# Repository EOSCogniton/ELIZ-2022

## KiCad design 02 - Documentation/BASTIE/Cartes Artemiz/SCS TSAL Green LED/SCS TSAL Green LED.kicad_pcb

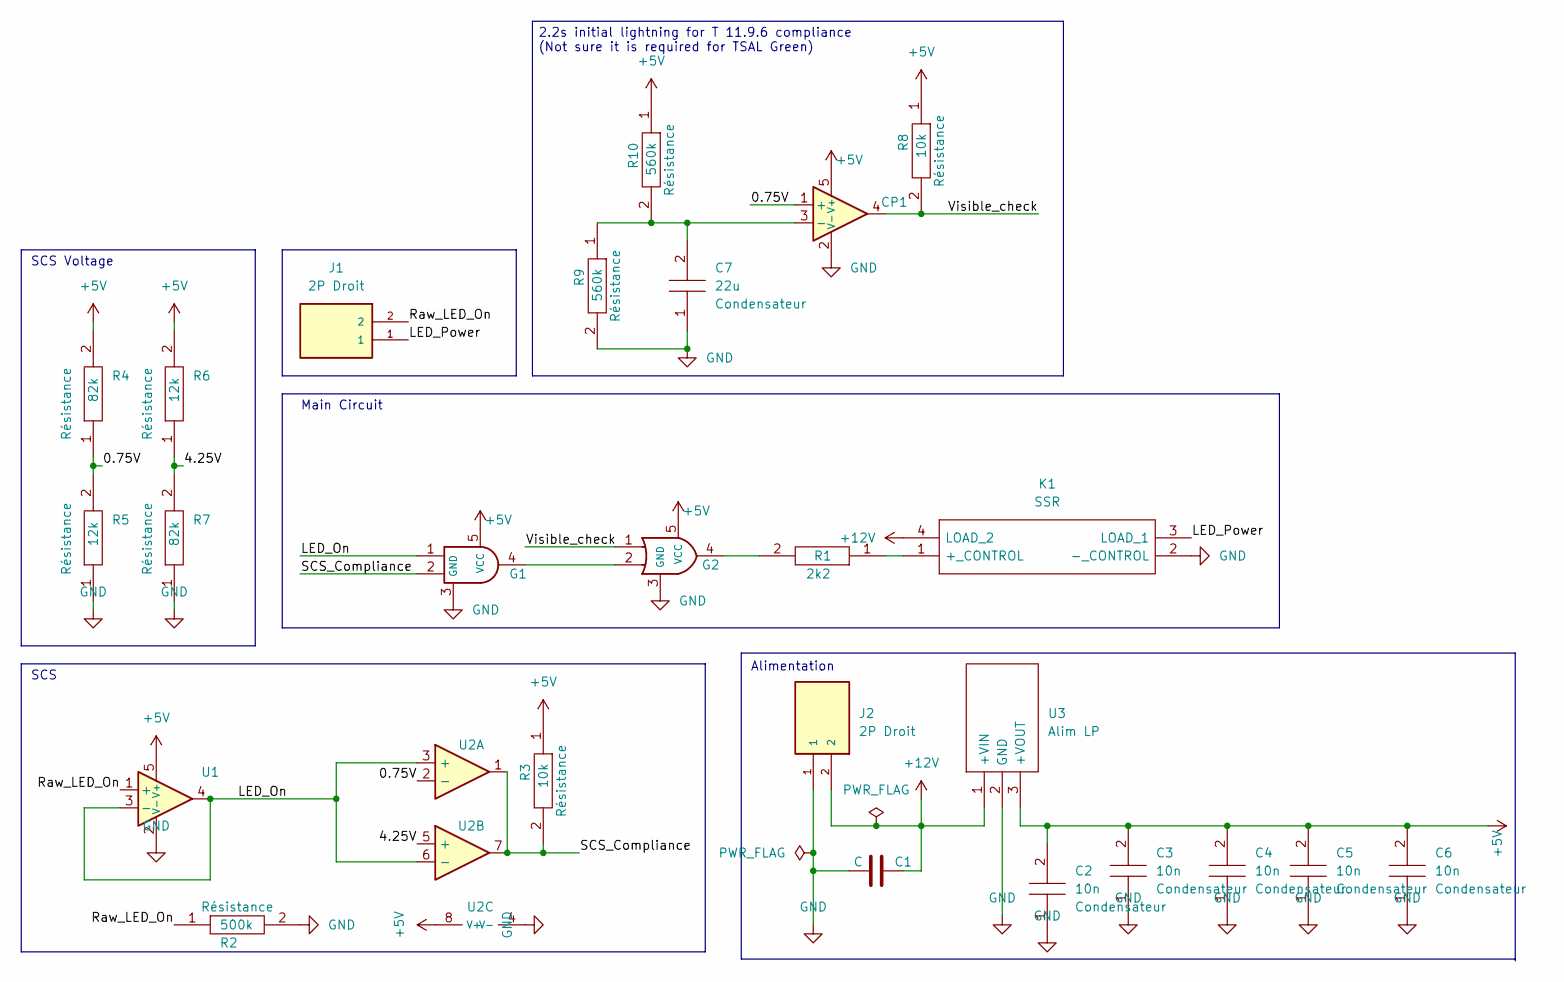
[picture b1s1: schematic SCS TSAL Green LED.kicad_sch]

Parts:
C1: C; CP_Radial_D5.0mm_P2.00mm
C2, C3, C4, C5, C6: 10n; CAPC2012X130N; Manufacturer_Part_Number 0805Y1000104JXT
C7: 22u; CAPC2012X130N; Manufacturer_Part_Number 0805Y1000104JXT
CP1: Comparator; SOT-353_SC-70-5; Manufacturer_Part_Number LMV331M7/NOPB; Mouser Part Number 926-LMV331M7/NOPB
G1: Gate AND SN74AHCT1G08DBVR; SOT95P280X145-5N; Manufacturer_Part_Number SN74AHCT1G08DBVR; Mouser Part Number 595-SN74AHCT1G08DBVR
G2: Gate OR SN74AHCT1G32DBVR; SOT95P280X145-5N; Manufacturer_Part_Number SN74AHCT1G32DBVR; Mouser Part Number 595-SN74AHCT1G32DBVR
J1, J2: 2P Droit 2-11-2022; MOLEX_22-11-2022; PARTREV BD8
K1: SSR CPC1394GR; CPC1394GR; Manufacturer_Part_Number CPC1394GR; Mouser Part Number 849-CPC1394GR
R1: 2k2; RESC3216X70N; Manufacturer_Part_Number RK73H2BLTDD2152F; Mouser Part Number N/A
R2: 500k; RESC3216X70N; Manufacturer_Part_Number RK73H2BLTDD2152F; Mouser Part Number N/A
R3, R8: 10k; RESC3216X70N; Manufacturer_Part_Number RK73H2BLTDD2152F; Mouser Part Number N/A
R4, R7: 82k; RESC3216X70N; Manufacturer_Part_Number RK73H2BLTDD2152F; Mouser Part Number N/A
R5, R6: 12k; RESC3216X70N; Manufacturer_Part_Number RK73H2BLTDD2152F; Mouser Part Number N/A
R9, R10: 560k; RESC3216X70N; Manufacturer_Part_Number RK73H2BLTDD2152F; Mouser Part Number N/A
U1: ${SIM.PARAMS}; SOT-353_SC-70-5_Handsoldering; Manufacturer_Part_Number TLV9061QDCKRQ1; Mouser Part Number 595-TLV9061QDCKRQ1
U2: Opamp_Dual; TSSOP-8_4.4x3mm_P0.65mm; Manufacturer_Part_Number LMV393IPWR; Mouser Part Number 595-LMV393IPWR
U3: Alim LP TSR_0.5-2450; TSR-0.5-2433; Manufacturer_Part_Number TSR 0.5-2450; Mouser Part Number 495-TSR0.5-2450

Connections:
+5V: C2.2, C3.2, C4.2, C5.2, C6.2, CP1.5 (V+), G1.5 (VCC), G2.5 (VCC), R3.1, R4.2, R6.2, R8.1, R10.1, U1.5 (V+), U2.8 (V+), U3.3 (+VOUT)
+12V: C1.2, J2.2, K1.4 (LOAD_2), U3.1 (+VIN)
/0.75V: CP1.1 (+), R4.1, R5.2, U2.2 (-)
/4.25V: R6.1, R7.2, U2.5 (+)
/LED_On: G1.1, U1.3 (-), U1.4, U2.3 (+), U2.6 (-)
/LED_Power: J1.1, K1.3 (LOAD_1)
/Raw_LED_On: J1.2, R2.1, U1.1 (+)
/SCS_Compliance: G1.2, R3.2, U2.1, U2.7
/Visible_check: CP1.4, G2.1, R8.2
GND: C1.1, C2.1, C3.1, C4.1, C5.1, C6.1, C7.1, CP1.2 (V-), G1.3 (GND), G2.3 (GND), J2.1, K1.2 (-_CONTROL), R2.2, R5.1, R7.1, R9.2, U1.2 (V-), U2.4 (V-), U3.2 (GND)
unnamed: C7.2, CP1.3 (-), R9.1, R10.2
unnamed: G1.4, G2.2
unnamed: G2.4, R1.2
unnamed: K1.1 (+_CONTROL), R1.1

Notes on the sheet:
Alimentation
Main Circuit
SCS
SCS Voltage
2.2s initial lightning for T 11.9.6 compliance (Not sure it is required for TSAL Green)

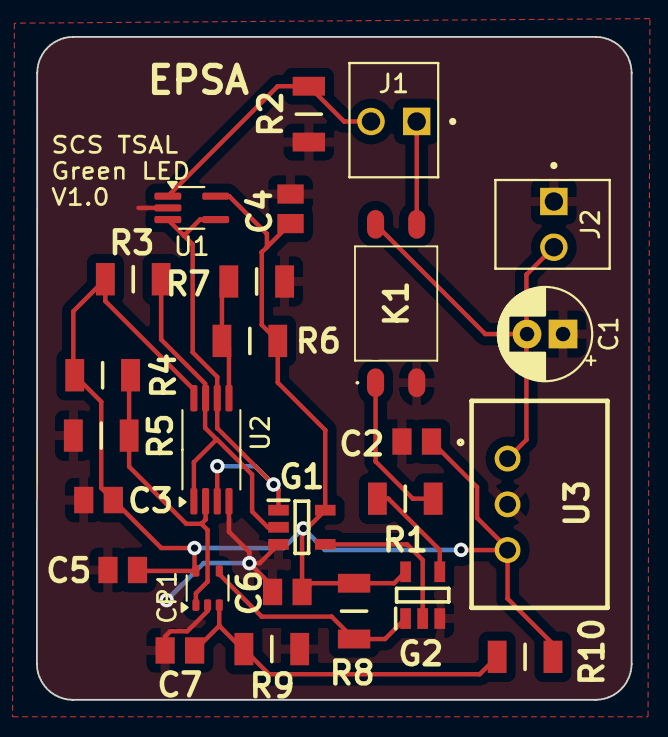
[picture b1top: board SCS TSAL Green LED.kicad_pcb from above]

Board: 2 copper layers, 33.0 x 36.8 mm, 26 parts (0 on the bottom side), 14 nets.

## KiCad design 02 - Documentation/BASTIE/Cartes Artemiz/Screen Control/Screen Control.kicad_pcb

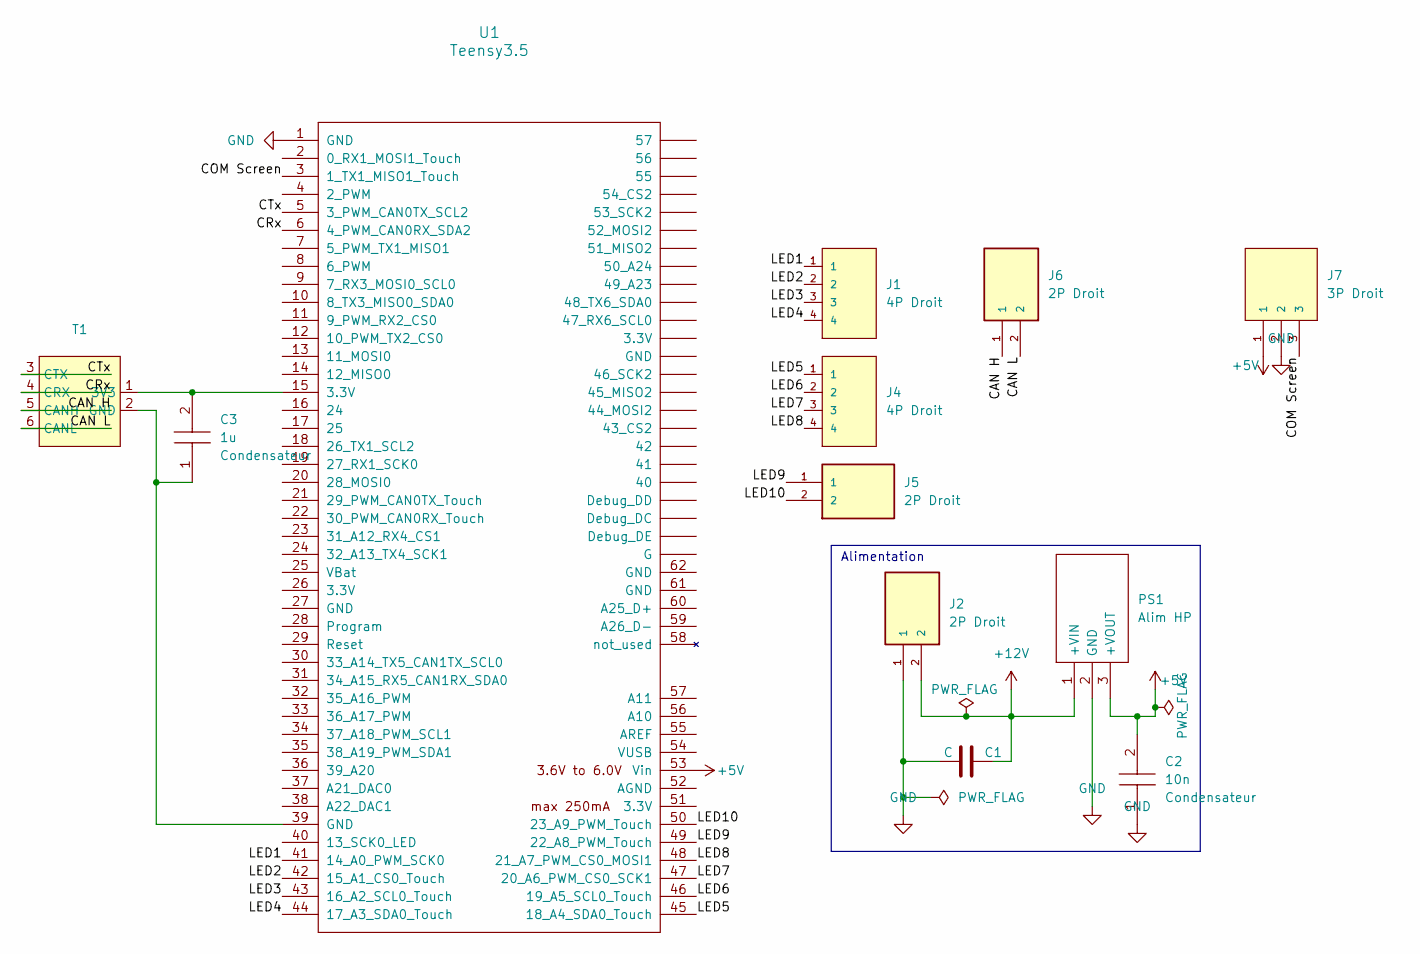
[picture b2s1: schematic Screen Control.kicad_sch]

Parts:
C1: C; CP_Radial_D5.0mm_P2.00mm
C2: 10n; CAPC2012X130N; Manufacturer_Part_Number 0805Y1000104JXT
C3: 1u; CAPC2012X130N; Manufacturer_Part_Number 0805Y1000104JXT
J1, J4: 4P Droit 22-11-2042; MOLEX_22-11-2042; Manufacturer_Part_Number 22-11-2042; Mouser Part Number 538-22-11-2042
J2, J5, J6: 2P Droit 2-11-2022; MOLEX_22-11-2022; PARTREV BD8
J7: 3P Droit 22-11-2032; MOLEX_22-11-2032; Manufacturer_Part_Number 22-11-2032; Mouser Part Number 538-22-11-2032
PS1: Alim HP TSR_2-2450; TSR-2; Manufacturer_Part_Number TSR 2-2450; Mouser Part Number 495-TSR2-2450
T1: CAN_Transceiver
U1: Teensy3.5; Teensy35_36

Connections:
+5V: C2.2, J7.1, PS1.3 (+VOUT), U1.53 (Vin)
+12V: C1.2, J2.2, PS1.1 (+VIN)
/CAN H: J6.1, T1.5 (CANH)
/CAN L: J6.2, T1.6 (CANL)
/COM Screen: J7.3, U1.3 (1_TX1_MISO1_Touch)
/CRx: T1.4 (CRX), U1.6 (4_PWM_CAN0RX_SDA2)
/CTx: T1.3 (CTX), U1.5 (3_PWM_CAN0TX_SCL2)
/LED1: J1.1, U1.41 (14_A0_PWM_SCK0)
/LED2: J1.2, U1.42 (15_A1_CS0_Touch)
/LED3: J1.3, U1.43 (16_A2_SCL0_Touch)
/LED4: J1.4, U1.44 (17_A3_SDA0_Touch)
/LED5: J4.1, U1.45 (18_A4_SDA0_Touch)
/LED6: J4.2, U1.46 (19_A5_SCL0_Touch)
/LED7: J4.3, U1.47 (20_A6_PWM_CS0_SCK1)
/LED8: J4.4, U1.48 (21_A7_PWM_CS0_MOSI1)
/LED9: J5.1, U1.49 (22_A8_PWM_Touch)
/LED10: J5.2, U1.50 (23_A9_PWM_Touch)
GND: C1.1, C2.1, J2.1, J7.2, PS1.2 (GND), U1.1 (GND)
unnamed: C3.2, T1.1 (3V3), U1.15 (3.3V)
unnamed: C3.1, T1.2 (GND), U1.39 (GND)

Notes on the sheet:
Alimentation

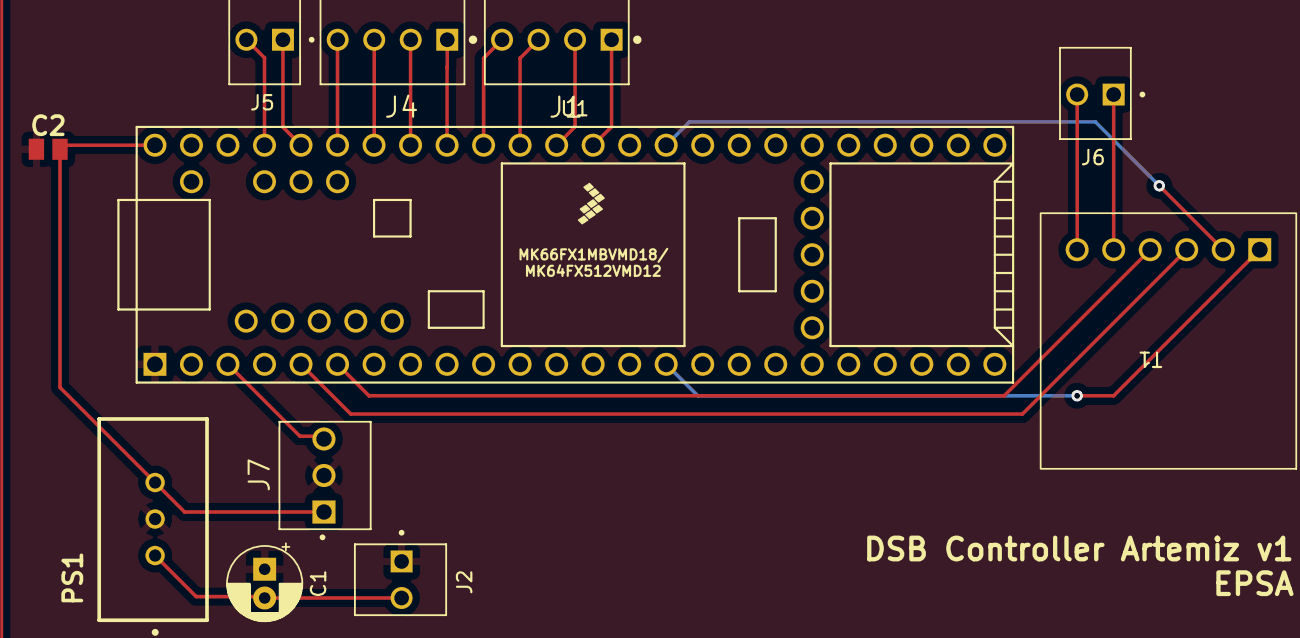
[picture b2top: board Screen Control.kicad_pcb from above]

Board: 2 copper layers, 11 parts (0 on the bottom side), 20 nets.

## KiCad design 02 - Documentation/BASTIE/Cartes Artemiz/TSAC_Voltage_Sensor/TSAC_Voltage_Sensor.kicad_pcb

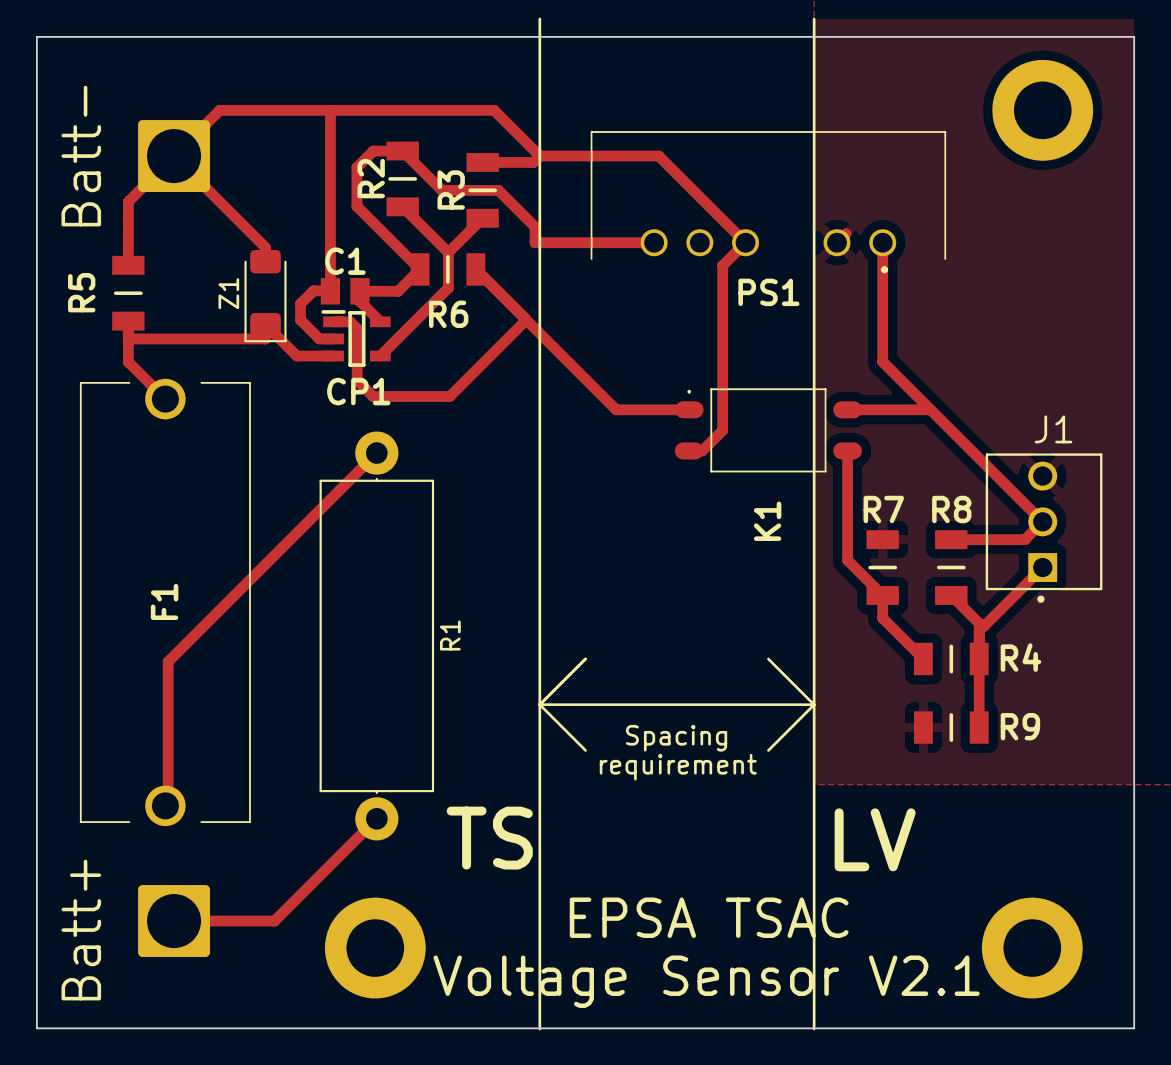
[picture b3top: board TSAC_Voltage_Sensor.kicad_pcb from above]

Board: 2 copper layers, 61.0 x 55.1 mm, 18 parts (0 on the bottom side), 11 nets.

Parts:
C1: Condensateur 0805Y1000104JXT; CAPC2012X130N
CP1: Comparateur TS391ILT; SOT95P280X145-5N
F1: Fuse; 0PTF0078P
J1: 3P Droit 22-11-2032; MOLEX_22-11-2032
K1: SSR CPC1394GR; CPC1394GR
PS1: Alim Iso PDM2-S5-S5-S; PDM2S5S5S
R1: 820k; R_Axial_DIN0617_L17.0mm_D6.0mm_P20.32mm_Horizontal
R2: 1k2; RESC3216X70N
R3: 1k; RESC3216X70N
R4: 3k9; RESC3216X70N
R5: 33k; RESC3216X70N
R6: 2k7; RESC3216X70N
R7: 2k; RESC3216X70N
R8, R9: 8k2; RESC3216X70N
TP1, TP2: type="R" model="TestPoint" lib=""; SolderWire-2.5sqmm_1x01_D2.4mm_OD3.6mm
Z1: Zener TZM5224B-GS08; D_MiniMELF

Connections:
0: C1.1, CP1.2 (VCC-), K1.2 (-_CONTROL), PS1.4 (0V), R3.2, R5.1, TP2.1, Z1.2
+5V: C1.2, CP1.5 (VCC+), PS1.6 (+VO), R2.2, R6.2
+5VA: J1.2, K1.4 (LOAD_2), PS1.1 (VIN), R8.2
+BATT: R1.2, TP1.1
Comp: CP1.1 (OUT), K1.1 (+_CONTROL), R6.1
Exit: J1.1, R4.2, R8.1, R9.2
GND: J1.3, PS1.2 (GND), R7.1, R9.1
unnamed: CP1.4 (IN+), R2.1, R3.1
unnamed: CP1.3 (IN-), F1.2, R5.2, Z1.1
unnamed: F1.1, R1.1
Raw_Exit: K1.3 (LOAD_1), R4.1, R7.2

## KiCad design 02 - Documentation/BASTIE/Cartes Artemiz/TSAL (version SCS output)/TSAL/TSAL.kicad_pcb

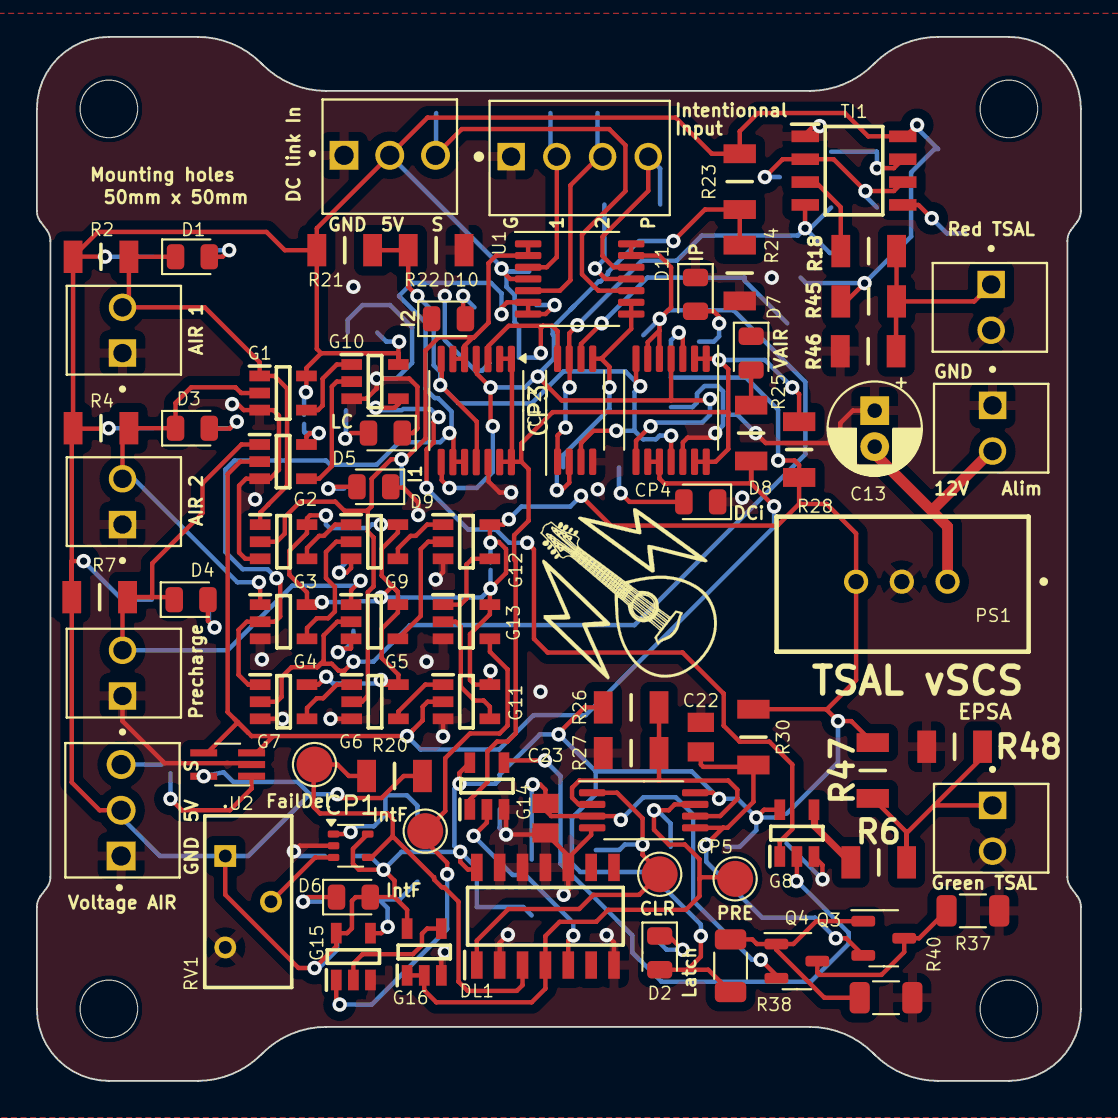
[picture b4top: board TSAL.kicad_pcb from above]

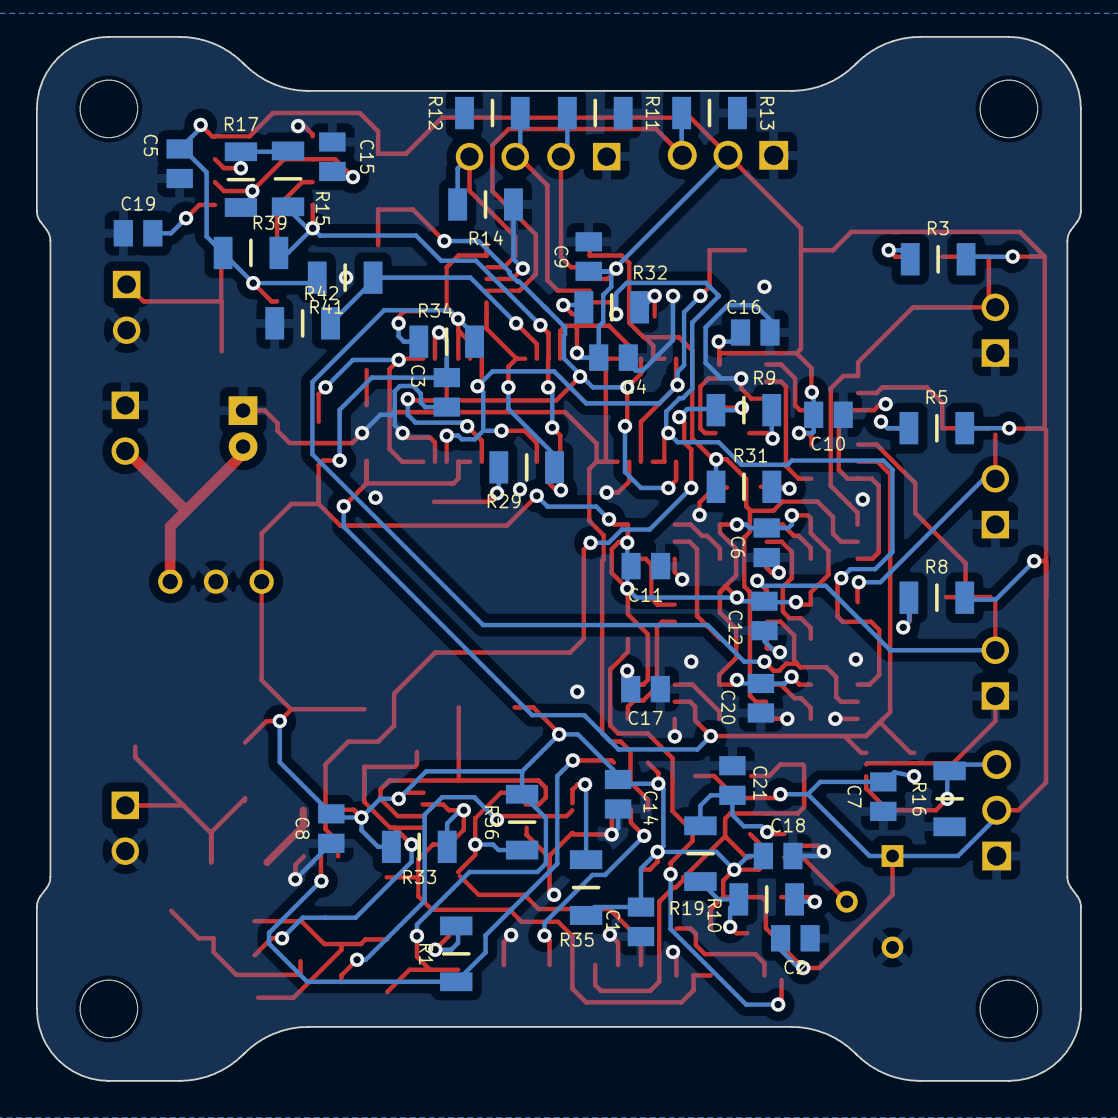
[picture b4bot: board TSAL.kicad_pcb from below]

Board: 2 copper layers, 58.0 x 58.0 mm, 127 parts (44 on the bottom side), 65 nets.

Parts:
C1, C2, C3, C4, C5, C6, C7, C8, C9, C10, C11, C12, C14, C16, C17, C18, C20: 10u; CAPC2012X130N
C13: C; CP_Radial_D5.0mm_P2.00mm
C15, C23: 1u; CAPC2012X130N
C19: 0.01u; CAPC2012X130N
C21, C22: 2.2u; CAPC2012X130N
CP1: Comparator; SOT-353_SC-70-5
CP2, CP5: Comparator_Dual; TSSOP-8_4.4x3mm_P0.65mm
CP3, CP4: Comparator_Quad; TSSOP-14_4.4x5mm_P0.65mm
D1, D2, D3, D4, D5, D6, D7, D8, D9, D10, D11: LED; LED_0805_2012Metric
DL1: Bascule D SN74HCS72QDRQ1; SOIC127P600X175-14N
G1, G2, G3, G4, G5, G6, G8, G10, G11, G14: Gate AND SN74AHCT1G08DBVR; SOT95P280X145-5N
G7, G9, G12, G15: Gate OR SN74AHCT1G32DBVR; SOT95P280X145-5N
G13, G16: Gate NOR SN74AHCT1G02DBVR; SOT95P280X145-5N
H1, H2, H3, H4: MountingHole; MountingHole_3.2mm_M3
J1, J2, J3, J5, J6, J9: 2P Droit 2-11-2022; MOLEX_22-11-2022
J4, J8: 3P Droit 22-11-2032; MOLEX_22-11-2032
J7: 4P Droit 22-11-2042; MOLEX_22-11-2042
PS1: Alim HP TSR_2-2450; TSR-2
Q3, Q4: PMOS SI2343CDS-T1-GE3; SOT-23-3
R1, R3, R5, R8, R9, R10, R25, R29, R31, R32, R34: 500; RESC3216X70N
R2, R4, R7, R20, R28, R39: 10k; RESC3216X70N
R6, R18: 3k9; RESC3216X70N
R11, R12, R13, R14, R16, R30, R35: 500k; RESC3216X70N
R15: 2k; RESC3216X70N
R17: 200k; RESC3216X70N
R19: 390k; RESC3216X70N
R21, R24, R41, R42: 12k; RESC3216X70N
R22, R23: 82k; RESC3216X70N
R26: 100k; RESC3216X70N
R27: 50k; RESC3216X70N
R33, R36: 5k; RESC3216X70N
R37: 1k; R_1206_3216Metric
R38: 10k; R_1206_3216Metric
R40: 100k; R_1206_3216Metric
R45, R46, R47, R48: 8k2; RESC3216X70N
RV1: Varystor 3296Y-1-223LF; 3296Y1223LF
Ref**: Val**; Mandolule Silk
TI1: Timer 555 LM555CMX_NOPB; SOIC127P600X175-8N
TP1, TP2, TP3, TP4: type="R" model="TestPoint" lib=""; TestPoint_Pad_D2.0mm
U1: Opamp_Quad; TSSOP-14_4.4x5mm_P0.65mm
U2: Opamp; SOT-353_SC-70-5_Handsoldering

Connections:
+5V: C1.2, C2.2, C3.2, C4.2, C5.2, C6.2, C7.2, C8.2, C9.2, C10.2, C11.2, C12.2, C14.2, C16.2, C17.2, C18.2, C20.2, CP1.5 (V+), CP2.8 (V+), CP3.3 (V+), CP4.3 (V+), CP5.8 (V+), D2.2 (A), D6.2 (A), DL1.14 (VCC), G1.5 (VCC), G2.5 (VCC), G3.5 (VCC), G4.5 (VCC), G5.5 (VCC), G6.5 (VCC), G7.5 (VCC), G8.5 (VCC), G9.5 (VCC), G10.5 (VCC), G11.5 (VCC), G12.5 (VCC), G13.5 (VCC), G14.5 (VCC), G15.5 (VCC), G16.5 (VCC), J4.2, J8.2, PS1.3 (+VOUT), R2.2, R3.2, R4.2, R5.2, R7.2, R8.2, R20.2, R21.2, R23.2, R26.2, R28.1, R30.2, R33.2, R35.2, R36.2, R38.1, R39.1, R41.2, R45.2, R47.2, RV1.1 (CCW), TI1.8 (+VCC), U1.4 (V+), U2.5 (V+)
+12V: C13.2, J6.2, PS1.1 (+VIN)
/0.75V: CP3.4 (-), CP3.8 (-), CP4.4 (-), CP4.8 (-), R23.1, R24.2
/2.5V: CP2.6 (-), R41.1, R42.2
/4.25V: CP2.3 (+), CP3.7 (+), CP3.11 (+), CP4.7 (+), CP4.11 (+), R21.1, R22.2
/AIR_1: D1.1 (K), G1.1, G3.1, J1.2, R2.1
/AIR_2: D3.1 (K), G1.2, G4.1, J2.2, R4.1
/CLR: CP5.1, DL1.1 (1~CLR), R36.1, TP4.1
/Clign: R18.1, TI1.3 (OUTPUT)
/DC-Link_In: CP2.2 (-), CP2.5 (+), R29.2, U1.8, U1.9 (-)
/DC-Link_In_SCS: CP2.1, CP2.7, R15.2, R39.2, TI1.4 (RESET)
/INT: DL1.5 (1Q), G14.2
/Int_AIR_1: CP3.5 (+), CP3.6 (-), G3.2, G6.2, R31.2, U1.1, U1.2 (-)
/Int_AIR_2: CP3.9 (+), CP3.10 (-), G4.2, G7.1, R32.2, U1.6 (-), U1.7
/Int_PreCharge: CP4.5 (+), CP4.6 (-), G5.2, G7.2, R34.2, U1.13 (-), U1.14
/Int_del: CP1.4, DL1.3 (1~CLK), R20.1, TP2.1
/Int_log: G13.4, G15.1, TP1.1
/Lightning_cond: G8.1, G10.4, R9.1
/PRE: CP5.7, DL1.4 (1~PRE), G16.1, G16.2, R33.1, TP3.1
/PreCharge: D4.1 (K), G2.1, G5.1, J3.2, R7.1
/Raw_DC-Link_In: J8.3, R13.2, U1.10 (+)
/Raw_Int_AIR_1: J7.2, R11.2, U1.3 (+)
/Raw_Int_AIR_2: J7.3, R12.2, U1.5 (+)
/Raw_Int_PreCharge: J7.4, R14.2, U1.12 (+)
/Raw_VoltageAIR: J4.3, R16.2, U2.1 (+)
/SCS compliance: CP3.1, CP3.2, CP3.13, CP3.14, CP4.1, CP4.2, CP4.13, CP4.14, G14.1, R28.2
/VoltageAIR: CP4.9 (+), CP4.10 (-), G2.2, G11.2, R25.2, U2.3 (-), U2.4
/dis1: C22.2, CP5.5 (+), Q3.2, R30.1
/dis2: C23.2, CP5.3 (+), Q4.2, R35.1
/mid_Pot: CP5.2 (-), CP5.6 (-), R26.1, R27.2
GND: C1.1, C2.1, C3.1, C4.1, C5.1, C6.1, C7.1, C8.1, C9.1, C10.1, C11.1, C12.1, C13.1, C14.1, C15.1, C16.1, C17.1, C18.1, C19.1, C20.1, C21.2, C22.1, C23.1, CP1.2 (V-), CP2.4 (V-), CP3.12 (V-), CP4.12 (V-), CP5.4 (V-), D5.1 (K), D7.1 (K), D8.1 (K), D9.1 (K), D10.1 (K), D11.1 (K), DL1.2 (1D), DL1.7 (GND), DL1.10 (2~PRE), DL1.11 (2~CLK), DL1.12 (2D), DL1.13 (2~CLR), G1.3 (GND), G2.3 (GND), G3.3 (GND), G4.3 (GND), G5.3 (GND), G6.3 (GND), G7.3 (GND), G8.3 (GND), G9.3 (GND), G10.3 (GND), G11.3 (GND), G12.3 (GND), G13.3 (GND), G14.3 (GND), G15.3 (GND), G16.3 (GND), J1.1, J2.1, J3.1, J4.1, J5.2, J6.1, J7.1, J8.1, J9.2, PS1.2 (GND), R11.1, R12.1, R13.1, R14.1, R16.1, R22.1, R24.1, R27.1, R37.1, R40.2, R42.1, R46.1, R48.1, RV1.3 (CW), TI1.1 (GND), U1.11 (V-), U2.2 (V-)
unnamed: C21.1, CP1.1 (+), R19.2
unnamed: CP1.3 (-), RV1.2 (WIPER)
unnamed: D1.2 (A), R3.1
unnamed: D2.1 (K), R1.2
unnamed: D3.2 (A), R5.1
unnamed: D4.2 (A), R8.1
unnamed: D5.2 (A), R9.2
unnamed: D6.1 (K), R10.2
unnamed: D7.2 (A), R25.1
unnamed: D8.2 (A), R29.1
unnamed: D9.2 (A), R31.1
unnamed: D10.2 (A), R32.1
unnamed: D11.2 (A), R34.1
unnamed: G1.4, G10.1
unnamed: G3.4, G9.1
unnamed: G4.4, G9.2
unnamed: G6.1, G7.4
unnamed: G8.4, R6.1
unnamed: G2.4, G10.2
unnamed: G6.4, G11.1
unnamed: G11.4, G13.2
unnamed: G9.4, G12.1
unnamed: G5.4, G12.2
unnamed: G12.4, G13.1
unnamed: G8.2, G14.4, R1.1
unnamed: G15.2, G16.4
unnamed: G15.4, R10.1, R19.1
unnamed: J5.1, R6.2, R47.1, R48.2
unnamed: J9.1, R18.2, R45.1, R46.2
unnamed: Q3.1, Q4.1, R38.2, R40.1
unnamed: Q3.3, Q4.3, R37.2
unnamed: C19.2, TI1.5 (CONTROL_VOLTAGE)
unnamed: R15.1, R17.2, TI1.7 (DISCHARGE)
unnamed: C15.2, R17.1, TI1.2 (TRIGGER), TI1.6 (THRESHOLD)

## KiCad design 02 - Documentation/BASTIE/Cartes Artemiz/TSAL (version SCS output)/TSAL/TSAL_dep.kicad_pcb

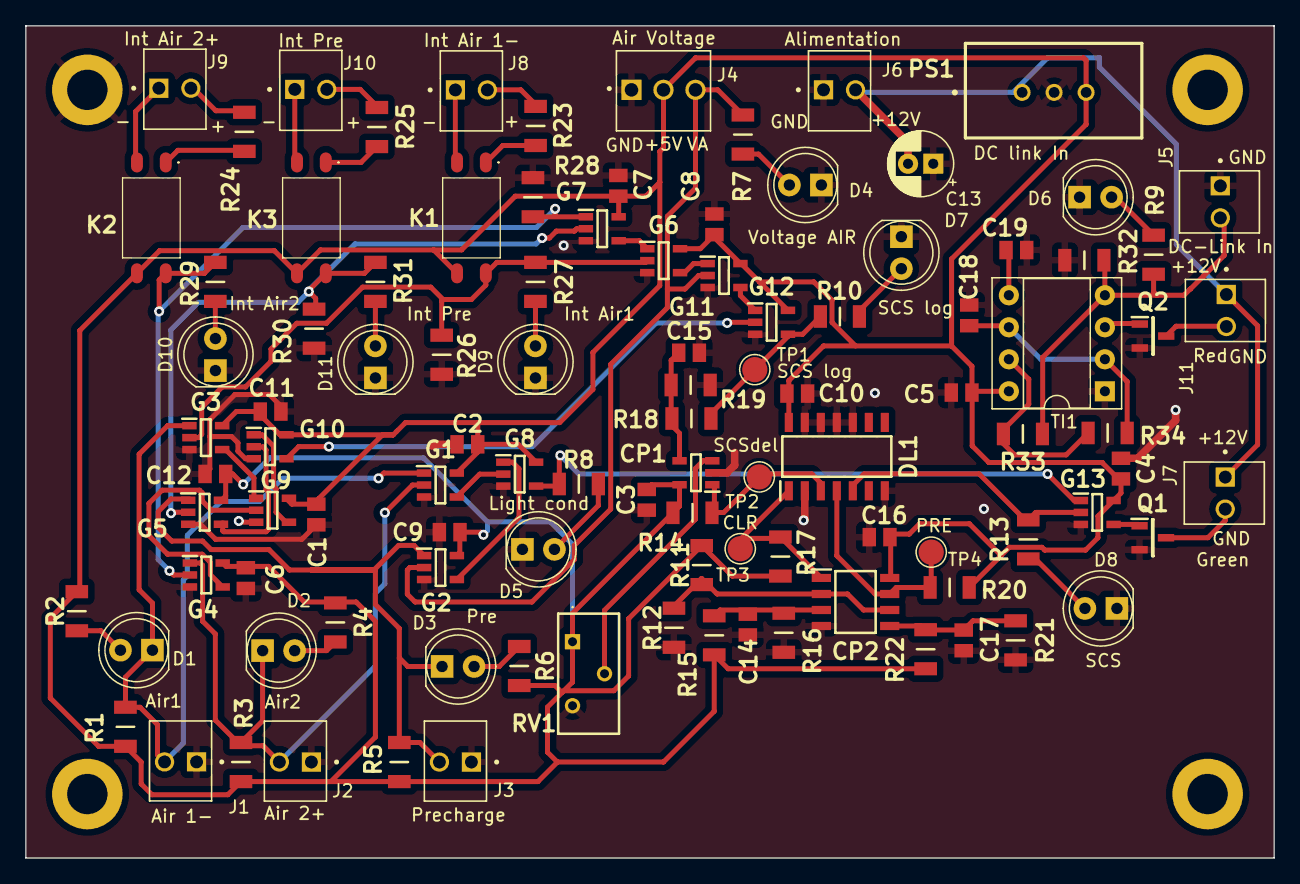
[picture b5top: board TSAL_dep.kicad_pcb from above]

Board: 2 copper layers, 99.1 x 66.0 mm, 103 parts (0 on the bottom side), 59 nets.

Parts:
C1, C2, C3, C4, C5, C6, C7, C8, C9, C10, C11, C12, C14, C15, C16, C17, C18, C19: Condensateur 0805Y1000104JXT; CAPC2012X130N
C13: C; CP_Radial_D5.0mm_P2.00mm
CP1: Comparateur TS391ILT; SOT95P280X145-5N
CP2: Comparateur Double LM393LVDR; SOIC127P600X175-8N
D1, D2, D3, D4, D5, D6, D7, D8, D9, D10, D11: LED; LED_D5.0mm
DL1: Bascule D SN74HCS72QDRQ1; SOIC127P600X175-14N
G1, G2, G3, G4, G5, G8, G13: Gate AND SN74AHCT1G08DBVR; SOT95P280X145-5N
G6: Gate NAND SN74AHCT1G00DBVR; SOT95P280X145-5N
G7, G9, G10, G12: Gate OR SN74AHCT1G32DBVR; SOT95P280X145-5N
G11: Gate NOR SN74AHCT1G02DBVR; SOT95P280X145-5N
J1, J2, J3, J5, J6, J7, J8, J9, J10, J11: 2P Droit 2-11-2022; MOLEX_22-11-2022
J4: 3P Droit 22-11-2032; MOLEX_22-11-2032
K1, K2, K3: SSR CPC1394GR; CPC1394GR
PS1: Alim HP TSR_2-2450; TSR-2
Q1, Q2: NMOS SQ2348ES-T1_GE3; SOT95P237X112-3N
R1, R2, R3, R4, R5, R6, R7, R8, R9, R10, R11, R12, R13, R14, R15, R16, R17, R18, R19, R20, R21, R22, R23, R24, R25, R26, R27, R28, R29, R30, R31, R32, R33, R34: Résistance RK73H2BLTDD2152F; RESC3216X70N
RV1: Varystor 3296Y-1-223LF; 3296Y1223LF
TI1: Timer 555 LM555CMX_NOPB; DIP-8_W7.62mm_Socket
TP1, TP2, TP3: type="R" model="TestPoint" lib=""; TestPoint_Pad_D2.0mm
TP4: etype="R" model="TestPoint" lib=""; TestPoint_Pad_D2.0mm

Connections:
0: C1.1, C2.1, C3.1, C4.1, C5.1, C6.1, C7.1, C8.1, C9.1, C10.1, C11.1, C12.1, C13.1, C14.1, C15.2, C16.2, C17.1, C18.1, C19.1, CP1.2 (VCC-), CP2.4 (GND), D4.1 (K), D5.1 (K), D6.1 (K), D7.1 (K), D8.1 (K), D9.1 (K), D10.1 (K), D11.1 (K), DL1.2 (1D), DL1.7 (GND), DL1.10 (2~PRE), DL1.11 (2~CLK), DL1.12 (2D), DL1.13 (2~CLR), G1.3 (GND), G2.3 (GND), G3.3 (GND), G4.3 (GND), G5.3 (GND), G6.3 (GND), G7.3 (GND), G8.3 (GND), G9.3 (GND), G10.3 (GND), G11.3 (GND), G12.3 (GND), G13.3 (GND), J1.1, J2.1, J3.1, J4.1, J5.1, J6.1, PS1.2 (GND), Q1.2, Q2.2, R12.1, R16.1, R19.2, R21.1, R26.2, R28.2, R30.2, R32.2, RV1.3 (CW), TI1.1 (GND)
+5V: C1.2, C2.2, C3.2, C4.2, C5.2, C6.2, C7.2, C8.2, C9.2, C10.2, C11.2, C12.2, C16.1, CP1.5 (VCC+), CP2.8 (V+), DL1.14 (VCC), G1.5 (VCC), G2.5 (VCC), G3.5 (VCC), G4.5 (VCC), G5.5 (VCC), G6.5 (VCC), G7.5 (VCC), G8.5 (VCC), G9.5 (VCC), G10.5 (VCC), G11.5 (VCC), G12.5 (VCC), G13.5 (VCC), J4.2, K1.3 (LOAD_1), K2.3 (LOAD_1), K3.3 (LOAD_1), PS1.3 (+VOUT), R1.2, R2.2, R3.2, R4.2, R5.2, R6.2, R11.2, R14.1, R15.2, R17.2, R20.2, R22.2, RV1.1 (CCW), TI1.8 (+VCC)
+12V: C13.2, J6.2, J7.1, J11.1, PS1.1 (+VIN)
AIR 1: D1.1 (K), G1.1 (A), G3.1 (A), J1.2, R1.1
AIR 2: D2.1 (K), G1.2 (B), G4.1 (A), J2.2, R3.1
CLR: CP2.1 (OUT1), DL1.1 (1~CLR), R17.1, TP3.1
Clign: Q2.1, TI1.3 (OUTPUT)
DC-Link In: J5.2, R9.2, R32.1, R33.2, TI1.4 (RESET)
Int AIR 1: G3.2 (B), G6.2 (B), K1.4 (LOAD_2), R26.1, R27.1
Int AIR 2: G4.2 (B), G7.1 (A), K2.4 (LOAD_2), R28.1, R29.1
Int PreCharge: G5.2 (B), G7.2 (B), K3.4 (LOAD_2), R30.1, R31.1
Lightning cond: G8.4 (Y), G13.1 (A), R8.1
unnamed: C15.1, CP1.4 (IN+), R18.2, R19.1
unnamed: CP1.3 (IN-), RV1.2 (WIPER)
unnamed: C14.2, CP2.3 (IN1+), R15.1, R16.2
unnamed: C17.2, CP2.5 (IN2+), R21.2, R22.1
unnamed: D1.2 (A), R2.1
unnamed: D2.2 (A), R4.1
unnamed: D3.2 (A), R6.1
unnamed: D4.2 (A), R7.1
unnamed: D5.2 (A), R8.2
unnamed: D6.2 (A), R9.1
unnamed: D7.2 (A), R10.2
unnamed: D8.2 (A), R13.2
unnamed: D9.2 (A), R27.2
unnamed: D10.2 (A), R29.2
unnamed: D11.2 (A), R31.2
unnamed: G1.4 (Y), G8.2 (B)
unnamed: G2.4 (Y), G8.1 (A)
unnamed: G3.4 (Y), G9.1 (A)
unnamed: G4.4 (Y), G9.2 (B)
unnamed: G6.1 (A), G7.4 (Y)
unnamed: G9.4 (Y), G10.1 (A)
unnamed: G5.4 (Y), G10.2 (B)
unnamed: G10.4 (Y), G12.2 (B)
unnamed: G6.4 (Y), G11.1 (A)
unnamed: G11.4 (Y), G12.1 (A)
unnamed: G13.4 (Y), Q1.1
unnamed: J7.2, Q1.3
unnamed: J8.2, R23.1
unnamed: J9.2, R24.1
unnamed: J10.2, R25.1
unnamed: J11.2, Q2.3
unnamed: K1.1 (+_CONTROL), R23.2
unnamed: J8.1, K1.2 (-_CONTROL)
unnamed: K2.1 (+_CONTROL), R24.2
unnamed: J9.1, K2.2 (-_CONTROL)
unnamed: K3.1 (+_CONTROL), R25.2
unnamed: J10.1, K3.2 (-_CONTROL)
unnamed: C19.2, TI1.5 (CONTROL_VOLTAGE)
unnamed: R33.1, R34.2, TI1.7 (DISCHARGE)
unnamed: C18.2, R34.1, TI1.2 (TRIGGER), TI1.6 (THRESHOLD)
PRE: CP2.7 (OUT2), DL1.4 (1~PRE), R20.1, TP4.1
PreCharge: D3.1 (K), G2.1 (A), G5.1 (A), J3.2, R5.1
SCS: DL1.5 (1Q), G13.2 (B), R13.1
SCS del: CP1.1 (OUT), DL1.3 (1~CLK), R14.2, TP2.1
SCS log: G12.4 (Y), R10.1, R18.1, TP1.1
VoltageAIR: G2.2 (B), G11.2 (B), J4.3, R7.2
mid Pot: CP2.2 (IN1-), CP2.6 (IN2-), R11.1, R12.2
